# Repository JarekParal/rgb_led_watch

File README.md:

# rgb_led_watch

RGB LED watch base on intelligent LED WS2812.

[Presentation video](https://youtu.be/sHXETtNtYNM)

License: [CC BY-SA 4.0](https://creativecommons.org/licenses/by-sa/4.0/?)

## Schema

## Board

## Other photos

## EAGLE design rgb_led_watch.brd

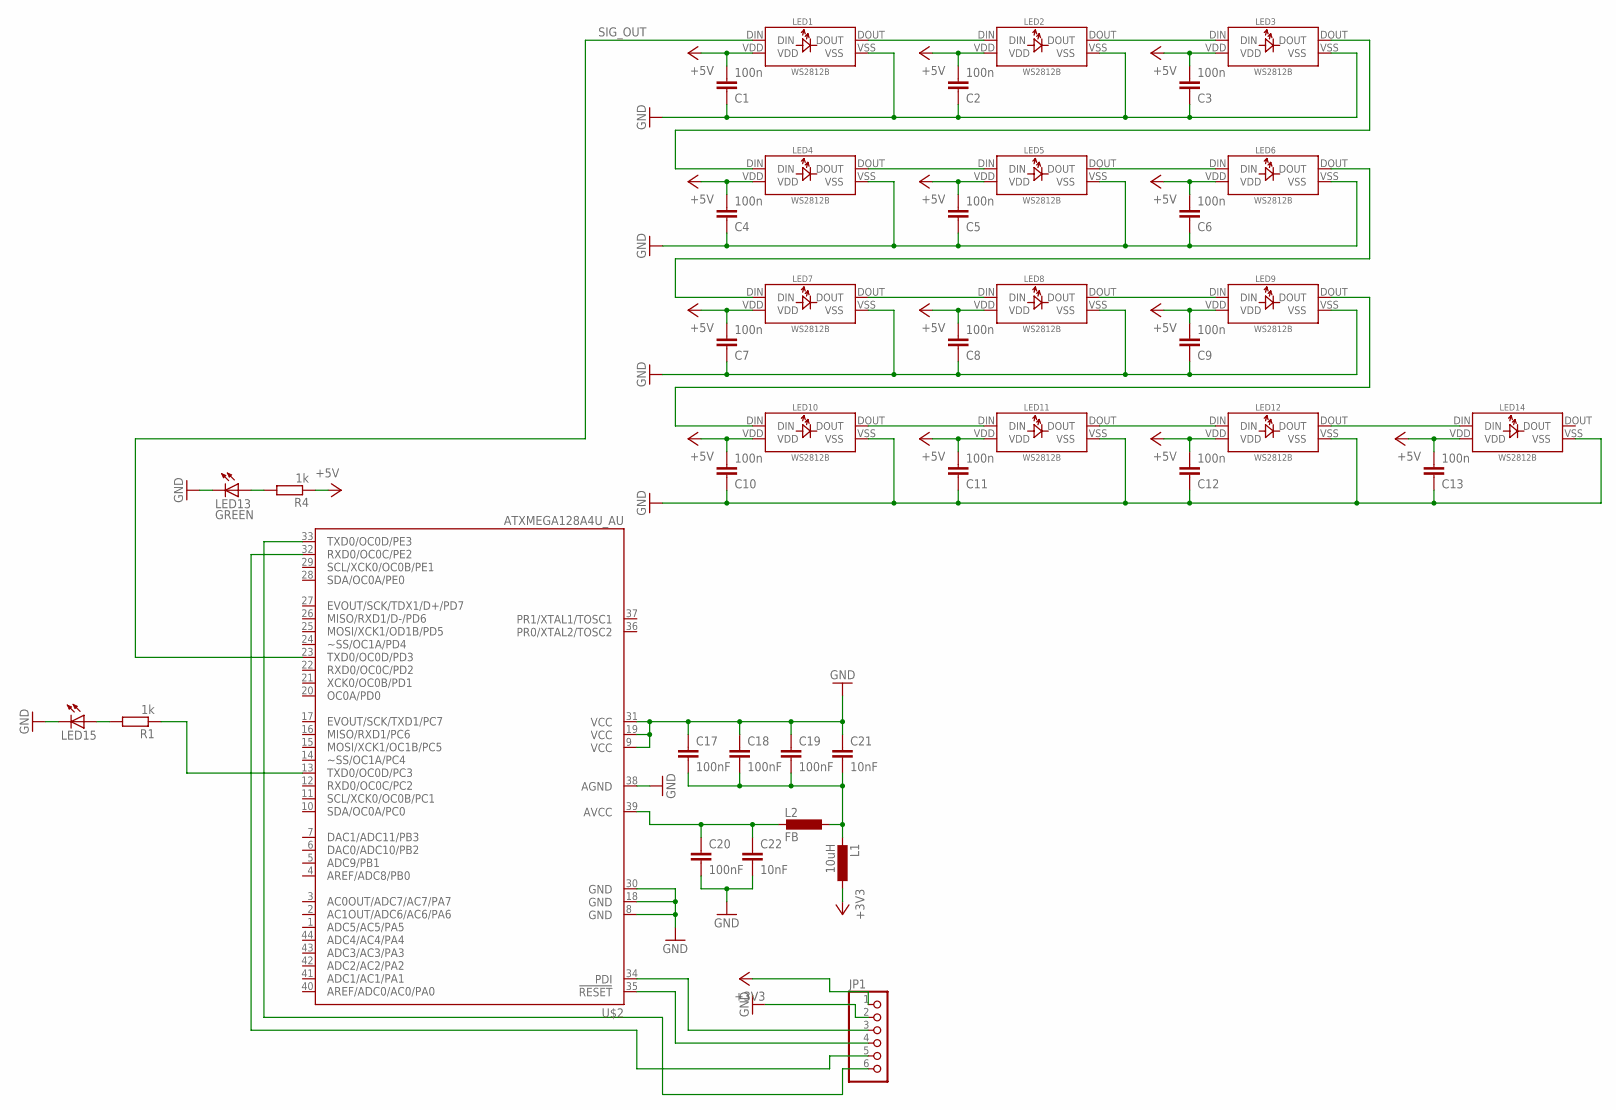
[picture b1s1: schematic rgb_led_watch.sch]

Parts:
C1, C2, C3, C4, C5, C6, C7, C8, C9, C10, C11, C12, C13: 100n; C0603
C17, C18, C19, C20: 100nF; C0306
C21, C22: 10nF; C0805
JP1: PINHD-1X6/90; 1X06/90
L1: 10uH; R0805
L2: FB; R0603
LED1, LED2, LED3, LED4, LED5, LED6, LED7, LED8, LED9, LED10, LED11, LED12, LED14: WS2812B
LED13: GREEN; CHIPLED_0603
LED15: LED5MM
R1, R4: 1k; R0603
U$2: ATXMEGA128A4U_AU; TQFP44

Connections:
+3V3: JP1.1, L1.1; also elsewhere on the board
+5V: C1.2, C2.2, C3.2, C4.2, C5.2, C6.2, C7.2, C8.2, C9.2, C10.2, C11.2, C12.2, C13.2, LED1.VDD, LED2.VDD, LED3.VDD, LED4.VDD, LED5.VDD, LED6.VDD, LED7.VDD, LED8.VDD, LED9.VDD, LED10.VDD, LED11.VDD, LED12.VDD, LED14.VDD, R4.1
GND: C1.1, C2.1, C3.1, C4.1, C5.1, C6.1, C7.1, C8.1, C9.1, C10.1, C11.1, C12.1, C13.1, C17.1, C18.1, C19.1, C20.2, C21.1, C22.2, JP1.2, LED1.VSS, LED2.VSS, LED3.VSS, LED4.VSS, LED5.VSS, LED6.VSS, LED7.VSS, LED8.VSS, LED9.VSS, LED10.VSS, LED11.VSS, LED12.VSS, LED13.C, LED14.VSS, LED15.K (C), U$2.8 (GND1), U$2.9 (VCC1), U$2.18 (GND2), U$2.19 (VCC2), U$2.30 (GND3), U$2.31 (VCC3), U$2.38 (AGND); also elsewhere on the board
LED1: LED6.DOUT, LED7.DIN
LED2: LED9.DOUT, LED10.DIN
LED3: LED3.DOUT, LED4.DIN
unnamed: C17.2, C18.2, C19.2, C21.2, L1.2, L2.1
unnamed: LED13.A, R4.2
unnamed: LED1.DOUT, LED2.DIN
unnamed: LED4.DOUT, LED5.DIN
unnamed: LED2.DOUT, LED3.DIN
unnamed: LED5.DOUT, LED6.DIN
unnamed: LED7.DOUT, LED8.DIN
unnamed: LED8.DOUT, LED9.DIN
unnamed: LED10.DOUT, LED11.DIN
unnamed: LED11.DOUT, LED12.DIN
unnamed: C20.1, C22.1, L2.2, U$2.39 (AVCC)
unnamed 17: JP1.3, U$2.34 (PDI_DATA); also elsewhere on the board
unnamed 18: JP1.6, U$2.33 (PE3); also elsewhere on the board
unnamed 19: JP1.5, U$2.32 (PE2); also elsewhere on the board
unnamed 20: U$2.35 (RESET); also elsewhere on the board
unnamed: LED12.DOUT, LED14.DIN
unnamed: LED15.A, R1.2
unnamed: R1.1, U$2.13 (PC3)
SIG_OUT: LED1.DIN, U$2.23 (PD3)

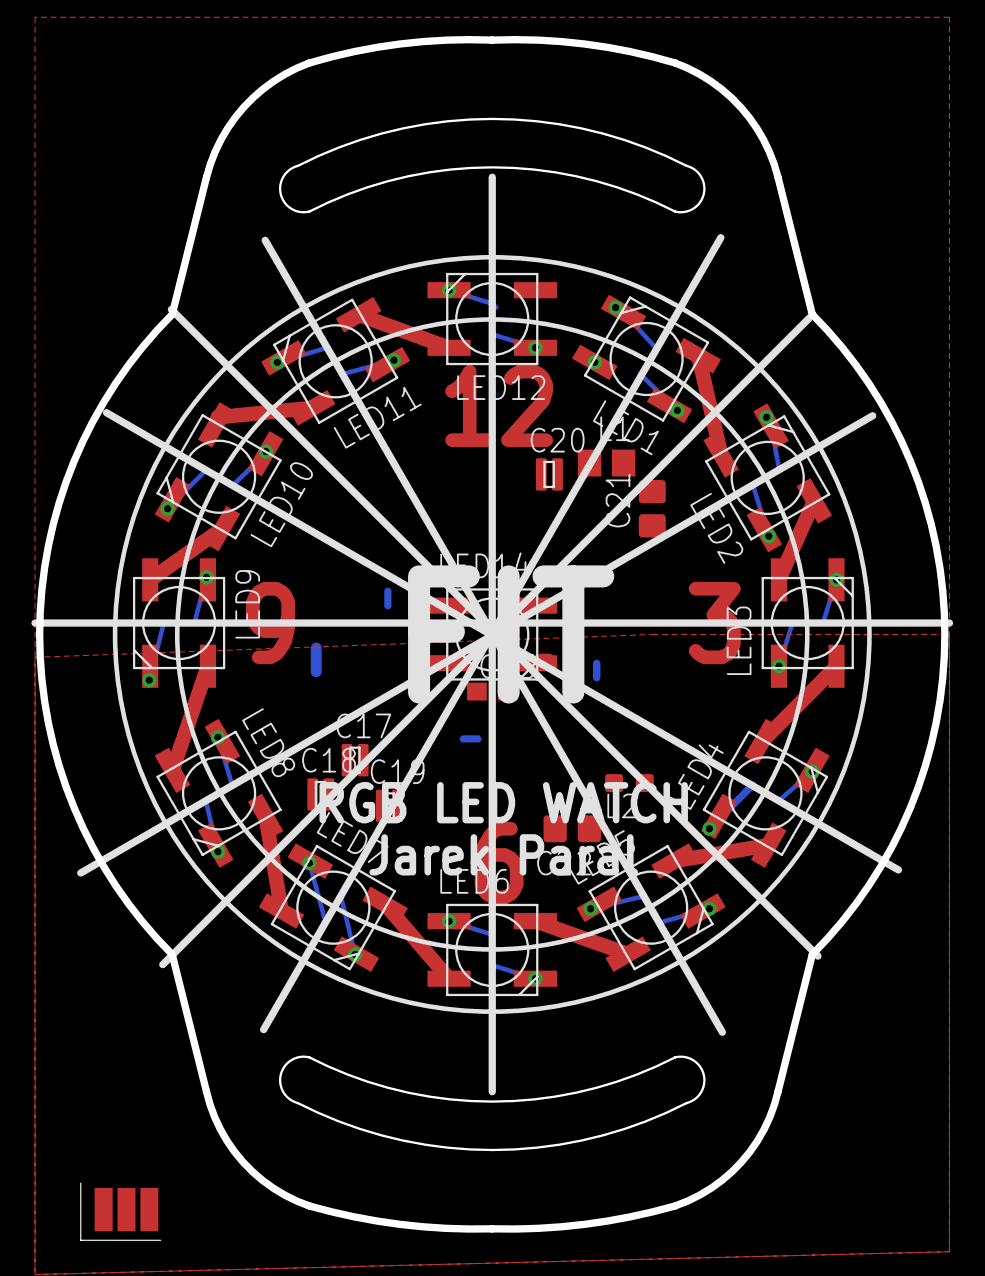
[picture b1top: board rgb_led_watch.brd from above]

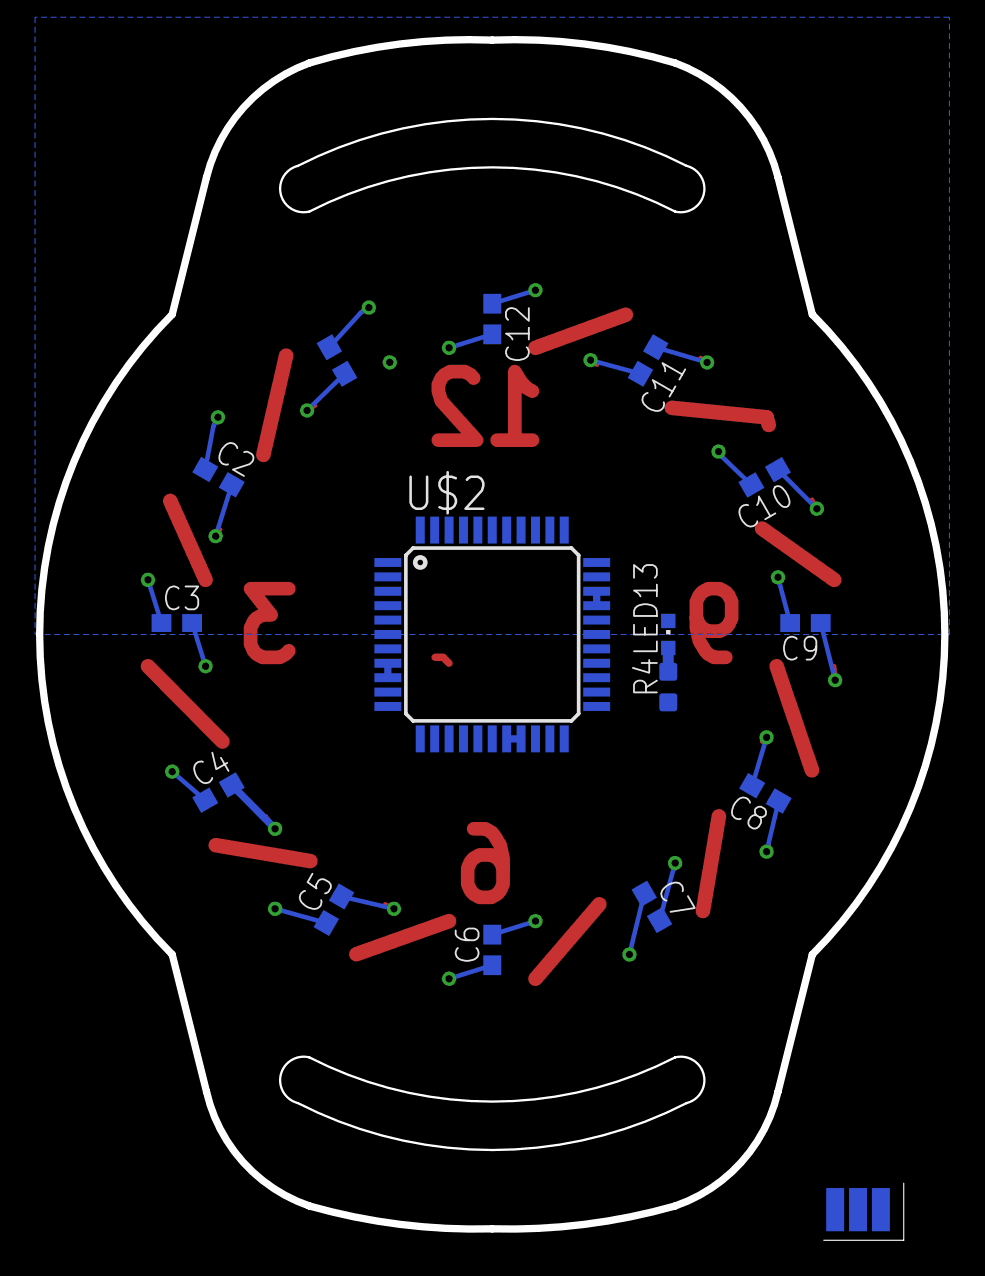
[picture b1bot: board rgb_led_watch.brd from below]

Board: 2 copper layers, 50.3 x 66.5 mm, 38 parts (15 on the bottom side), 23 nets.

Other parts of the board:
U$1: CON_PROG-6CORN; SMD-6-CORNER

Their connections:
+3V3: U$1.P$2; also elsewhere on the board
GND: U$1.P$6; also elsewhere on the board
unnamed 17: U$1.P$1; also elsewhere on the board
unnamed 18: U$1.P$3; also elsewhere on the board
unnamed 19: U$1.P$4; also elsewhere on the board
unnamed 20: U$1.P$5; also elsewhere on the board

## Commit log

2014-05-16 v1.0: prvni verze RGB LED hodinek (bez kapacitniho senzoru)
2014-05-17 v1.1: opraveny chyby (nezaroutovana draha, spatne nastaveni polygonu)
2014-05-17 v1.2: pridan kapacitni senzor
2014-05-17 v1.3: upraven tvar do podoby hodinek (pridelany ouska) - pripraveno do vyroby
2014-07-11 hodinky
2014-07-11 hodinky1
2019-04-05 Docs: add documentation images
2019-04-05 Add license CC BY-SA 4.0
